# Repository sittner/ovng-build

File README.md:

OVNG-BUILD
==========
This repo contains the stuff to build a OpenVarioNG:

- KiCad project for the PCB
- FreeCAD drawing that includes the sensor distribution block and a printable housing
- buildroot env to build the sd card image for installation

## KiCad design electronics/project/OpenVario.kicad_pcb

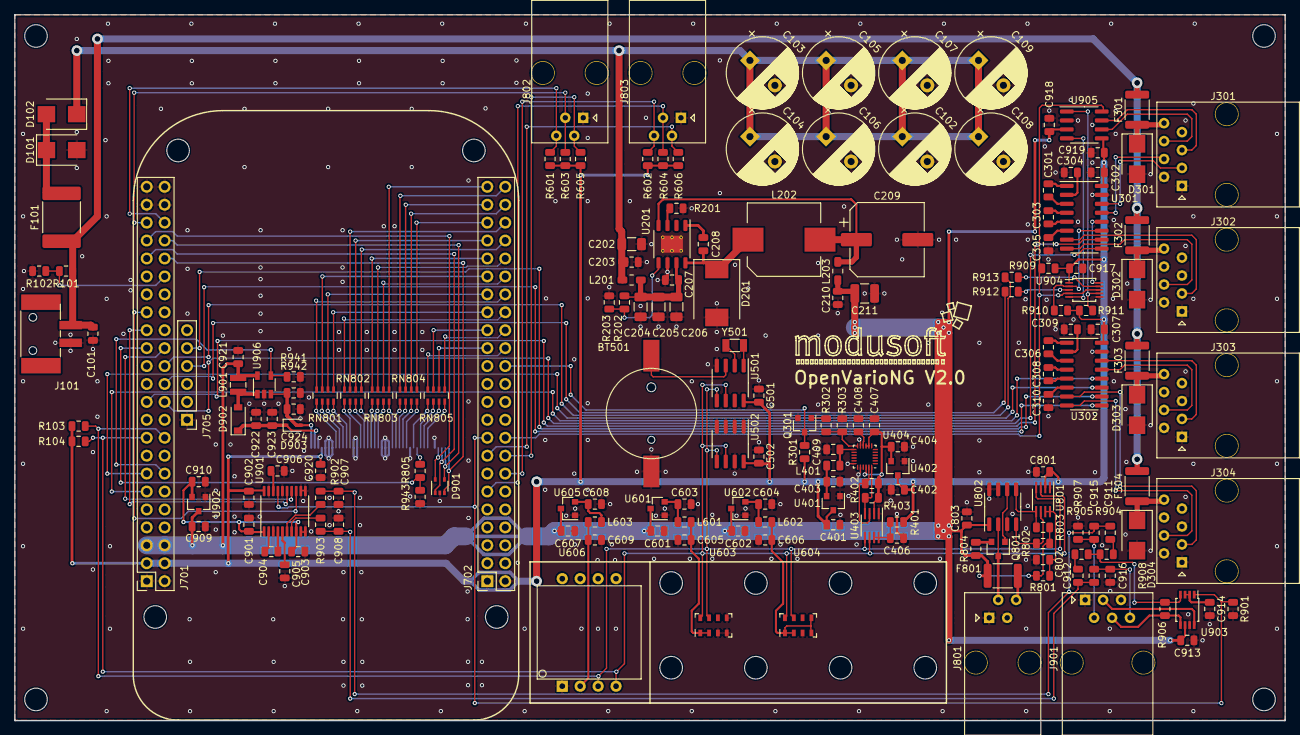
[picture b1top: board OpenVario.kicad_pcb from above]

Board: 2 copper layers, 180.0 x 100.0 mm, 200 parts (1 on the bottom side), 159 nets.

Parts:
BT501: CR-1220; BatteryHolder_HARWIN_S8411-45R_CR1220
C101, C203, C210, C302, C307, C406, C407, C408, C409, C501, C502, C605, C606, C609, C801, C802, C803, C901, C902, C903, C917, C918, C919, C920, C924: 100n; C_0805_2012Metric
C102, C103, C104, C105, C106, C107, C108, C109: 1000u/25V; CP_Radial_D10.0mm_P5.00mm
C202, C204, C205, C206: 4u7/50V; C_1206_3216Metric
C207: 1u/50V; C_0805_2012Metric
C208: 10n; C_0805_2012Metric
C209: 180u/16V; CP_Elec_10x7.9
C211: 47u/16V; C_1210_3225Metric
C301, C303, C304, C305, C306, C308, C309, C310, C401, C402, C403, C404, C601, C602, C603, C604, C607, C608, C909, C910, C913, C914, C915, C916, C922, C923: 1u; C_0805_2012Metric
C904, C905: 2u2; C_0805_2012Metric
C906, C921: 10u; C_0805_2012Metric
C907, C908: 2n2; C_0805_2012Metric
C911, C912: 470n; C_0805_2012Metric
D101: S3BB-13-F; D_SMB
D102: VS-20BQ030HM3/5BT; D_SMB
D201: SS36-E3/57T; D_SMC
D301, D302, D303, D304: S1BB-13-F; D_SMB
D901: PESD3V3L4UG; SOT-353_SC-70-5
D902: MBR0540; D_SOD-123
D903: MM3Z24VT1G; D_SOD-323
F101: 1.5A; Fuse_2920_7451Metric
F301, F302, F303, F304, F801: 300mA; Fuse_1812_4532Metric
H101, H102, H103, H104, H601, H602, H603, H604, H605, H606, H607, H608, H701, H702, H703, H704: M3; MountingHole_3.2mm_M3
J101: Power 12V; TerminalBlock_Phoenix_PTSM-0,5-2-HH-2.5-SMD_1x02-1MP_P2.50m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
J301: COM1; Modular-MEBP8-8S
J302: COM2; Modular-MEBP8-8S
J303: COM3; Modular-MEBP8-8S
J304: COM4; Modular-MEBP8-8S
J701: BeagleBone J9; PinSocket_2x23_P2.54mm_Vertical
J702: BeagleBone J8; PinSocket_2x23_P2.54mm_Vertical
J705: BeagleBone J1; PinHeader_1x06_P2.54mm_Vertical
J801: OneWire; Modular-MEBP4-4S
J802: ENC0; Modular-MEBP4-4S
J803: ENC1; Modular-MEBP4-4S
J901: Audio Out; Modular-MEBP6-6S
J902: DISP; TE_4-1734839-0_1x40-1MP_P0.5mm_Horizontal
L201, L203: 600R@100MHz/2A; WE_742792040
L202: 22u; L_Wuerth_WE-PDF_Handsoldering
L401, L601, L602, L603: 1k@100MHz; L_0805_2012Metric
L901: 10u; L_Wuerth_MAPI-2512
Q301: BC846; SOT-23
Q801: BSS84; SOT-23
R101: 120k; R_0805_2012Metric
R102, R301, R601, R602, R603, R604, R605, R606, R802, R803, R901, R909, R943: 10k; R_0805_2012Metric
R103, R104, R402, R403: 4k7; R_0805_2012Metric
R201: 61k9; R_0805_2012Metric
R202: 82k; R_0805_2012Metric
R203, R906: 20k; R_0805_2012Metric
R302, R303, R907, R908, R910, R911, R941: 100k; R_0805_2012Metric
R401, R801: 200k; R_0805_2012Metric
R804, R912, R913: 100R; R_0805_2012Metric
R805: 22R; R_0805_2012Metric
R902, R903: 470R; R_0805_2012Metric
R904, R905: 27k; R_0805_2012Metric
R942: 2R7; R_0805_2012Metric
RN801, RN802, RN803, RN804, RN805: 22R; R_Array_Concave_4x0603
U201: LM22670M-5_0; HSOP-8-1EP_3.9x4.9mm_P1.27mm_EP2.41x3.1mm_ThermalVias
U301, U302: MAX3232; SOIC-16_3.9x9.9mm_P1.27mm
U401, U402: MCP1700-1802E_SOT23; SOT-23
U403, U801: PCA9306; SSOP-8_2.95x2.8mm_P0.65mm
U404: ICM20948; QFN-24-1EP_3x3mm_P0.4mm_EP1.75x1.6mm_NP
U501: DS1338-33; SOIC-8_3.9x4.9mm_P1.27mm
U502: 24LC01; SOIC-8_3.9x4.9mm_P1.27mm
U601, U602, U605, U902: MCP1700-3302E_SOT23; SOT-23
U603, U604: MS5611; LGA-8_3x5mm_P1.25mm
U606: AMS5915
U802: DS2482-100; SOIC-8_3.9x4.9mm_P1.27mm
U901: PCM5101A; TSSOP-20_4.4x6.5mm_P0.65mm
U903: LM4990MM; TSSOP-8_3x3mm_P0.65mm
U904: TS3A24159DGSR; TSSOP-10_3x3mm_P0.5mm
U905: SN65HVDA540; SOIC-8_3.9x4.9mm_P1.27mm
U906: FAN5333B; TSOT-23-5
Y501: 32.768kHz/12.5pF; Crystal_SMD_3215-2Pin_3.2x1.5mm

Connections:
/5V Power Supply/Vin: C102.1, C103.1, C104.1, C105.1, C106.1, C107.1, C108.1, C109.1, C202.1, C203.1, D102.1, L201.1
/Audio Interface/+3V3: C302.2, C307.2, C401.1, C402.1, C501.2, C502.2, C801.2, C902.2, C917.2, C919.2, C920.2, J701.3, J701.4, J902.4, R103.1, R104.1, R301.2, R401.1, R601.1, R602.1, R603.1, R604.1, R605.1, R606.1, R909.1, R910.1, R911.1, U301.16, U302.16, U401.3, U402.3, U501.8, U502.8, U801.2, U901.20, U904.1, U905.5
/Audio Interface/+5V: C210.1, C211.1, C601.1, C602.1, C607.1, C803.2, C909.1, C913.1, C918.2, C921.2, F801.1, J701.5, J701.6, L203.2, L901.2, R801.2, R802.1, R803.1, R804.1, U601.3, U602.3, U605.3, U802.1, U902.3, U903.6, U905.3, U906.5
/Audio Interface/AUD_L: C907.1, C911.1, C915.1, R902.1
/Audio Interface/AUD_R: C908.1, C912.1, C916.1, R903.1
/Audio Interface/AVDD: C901.2, C903.2, C910.1, U901.1, U901.8, U902.2
/Audio Interface/BCK: J701.31, U901.13
/Audio Interface/DIN: J701.28, U901.14
/Audio Interface/ENA: J702.17, R901.2, U901.17, U903.1
/BeagleBone+Display/AIN5: J701.36, R101.2, R102.1
/BeagleBone+Display/BL_LED_A: C922.2, C923.2, D902.1, D903.1, J902.2
/BeagleBone+Display/BL_LED_K: C924.2, D903.2, J902.1, R942.2, U906.3
/BeagleBone+Display/GPIO0_7: J701.42, J802.4, R601.2
/BeagleBone+Display/GPIO0_20: J701.41, J802.3, R603.2
/BeagleBone+Display/GPIO0_26: J702.14, J803.4, R602.2
/BeagleBone+Display/GPIO1_13: J702.11, J803.3, R604.2
/BeagleBone+Display/GPIO1_14: J702.16, J802.2, R605.2
/BeagleBone+Display/GPIO1_15: J702.15, J803.2, R606.2
/BeagleBone+Display/GPIO2_1: J702.18, R909.2, U904.4, U904.8, U905.8
/BeagleBone+Display/I2C1_SCL: J701.17, R104.2, U403.6, U501.6, U502.6, U603.8, U604.8, U606.4, U801.3
/BeagleBone+Display/I2C1_SDA: J701.18, R103.2, U403.5, U501.5, U502.5, U603.7, U604.7, U606.3, U801.4
/BeagleBone+Display/I2S_LRCK: J701.29, U901.15
/BeagleBone+Display/IMU_IRQ: J702.26, Q301.3, R301.1
/BeagleBone+Display/LCD_BL_PWM: J701.14, R941.2, U906.4
/BeagleBone+Display/LCD_D0: J702.45, RN803.5
/BeagleBone+Display/LCD_D1: J702.46, RN804.8
/BeagleBone+Display/LCD_D2: J702.43, RN804.7
/BeagleBone+Display/LCD_D3: J702.44, RN804.6
/BeagleBone+Display/LCD_D4: J702.41, RN804.5
/BeagleBone+Display/LCD_D5: J702.42, RN802.7
/BeagleBone+Display/LCD_D6: J702.39, RN802.6
/BeagleBone+Display/LCD_D7: J702.40, RN802.5
/BeagleBone+Display/LCD_D8: J702.37, RN803.8
/BeagleBone+Display/LCD_D9: J702.38, RN803.7
/BeagleBone+Display/LCD_D10: J702.36, RN803.6
/BeagleBone+Display/LCD_D11: J702.34, RN801.8
/BeagleBone+Display/LCD_D12: J702.35, RN801.7
/BeagleBone+Display/LCD_D13: J702.33, RN801.6
/BeagleBone+Display/LCD_D14: J702.31, RN801.5
/BeagleBone+Display/LCD_D15: J702.32, RN802.8
/BeagleBone+Display/LCD_DISPEN: J701.27, R805.1, R943.2
/BeagleBone+Display/LCD_EN: J702.30, RN805.5
/BeagleBone+Display/LCD_HSYNC: J702.29, RN805.7
/BeagleBone+Display/LCD_PCLK: J702.28, RN805.8
/BeagleBone+Display/LCD_VSYNC: J702.27, RN805.6
/BeagleBone+Display/TOUCH_XL: D901.4, J701.40, J902.39
/BeagleBone+Display/TOUCH_XR: D901.5, J701.39, J902.37
/BeagleBone+Display/TOUCH_YD: D901.1, J701.37, J902.38
/BeagleBone+Display/TOUCH_YU: D901.3, J701.38, J902.40
/BeagleBone+Display/UART0_RXD: J705.4, U302.9
/BeagleBone+Display/UART0_TXD: J705.5, U302.10
/RS232 Interfaces/+12V: C101.1, F101.2, F301.2, F302.2, F303.2, F304.2, J101.2, R101.1
/RS232 Interfaces/CAN0_H: J301.5, U905.7
/RS232 Interfaces/CAN0_L: J301.6, U905.6
/RS232 Interfaces/CAN0_RXD_I: U904.5, U905.4
/RS232 Interfaces/CAN0_TXD_I: R911.2, U904.7, U905.1
/RS232 Interfaces/UART0_RXD: J701.26, R913.1
/RS232 Interfaces/UART0_RXD_I: U301.12, U904.10
/RS232 Interfaces/UART0_TXD: J701.24, R912.1
/RS232 Interfaces/UART0_TXD_I: R910.2, U301.11, U904.2
/RS232 Interfaces/UART1_RXD: J701.22, U301.9
/RS232 Interfaces/UART1_TXD: J701.21, U301.10
/RS232 Interfaces/UART2_RXD: J701.11, U302.12
/RS232 Interfaces/UART2_TXD: J701.13, U302.11
GND: BT501.2, C101.2, C102.2, C103.2, C104.2, C105.2, C106.2, C107.2, C108.2, C109.2, C202.2, C203.2, C204.2, C205.2, C206.2, C207.2, C209.2, C210.2, C211.2, C302.1, C304.1, C305.1, C307.1, C309.1, C310.1, C401.2, C402.2, C403.2, C404.2, C406.1, C407.1, C408.2, C409.1, C501.1, C502.1, C601.2, C602.2, C603.2, C604.2, C605.2, C606.2, C607.2, C608.2, C609.2, C801.1, C802.1, C803.1, C901.1, C902.1, C903.1, C905.2, C906.2, C907.2, C908.2, C909.2, C910.2, C913.2, C914.1, C917.1, C918.1, C919.1, C920.1, C921.1, C922.1, C923.1, C924.1, D101.2, D201.2, D301.2, D302.2, D303.2, D304.2, D901.2, J101.1, J301.1, J301.2, J302.1, J302.2, J302.5, J303.1, J303.2, J303.5, J304.1, J304.2, J304.5, J701.1, J701.2, J701.43, J701.44, J701.45, J701.46, J702.1, J702.2, J705.1, J801.1, J801.3, J802.1, J803.1, J901.1, J901.5, J902.3, J902.5, J902.6, J902.7, J902.13, J902.14, J902.21, J902.22, J902.23, J902.29, J902.36, Q301.2, R102.2, R201.2, R203.2, R303.1, R901.1, R907.1, R908.1, R941.1, R942.1, R943.1, U201.6, U201.9, U301.15, U302.15, U401.1, U402.1, U403.1, U404.11, U404.18, U404.20, U501.4, U502.1, U502.2, U502.3, U502.4, U502.7, U601.1, U602.1, U603.3, U603.4, U603.5, U604.3, U605.1, U606.1, U801.1, U802.3, U802.7, U802.8, U901.3, U901.9, U901.10, U901.11, U901.12, U901.16, U901.19, U902.1, U903.7, U904.6, U905.2, U906.2
unnamed: BT501.1, U501.3
unnamed: C204.1, C205.1, C206.1, C207.1, L201.2, R202.1, U201.7
unnamed: C208.1, D201.1, L202.1, U201.8
unnamed: C208.2, U201.1
unnamed: C209.1, L202.2, L203.1, U201.4
unnamed: C301.1, U301.1
unnamed: C301.2, U301.3
unnamed: C303.1, U301.4
unnamed: C303.2, U301.5
unnamed: C304.2, U301.2
unnamed: C305.2, U301.6
unnamed: C306.1, U302.1
unnamed: C306.2, U302.3
unnamed: C308.1, U302.4
unnamed: C308.2, U302.5
unnamed: C309.2, U302.2
unnamed: C310.2, U302.6
unnamed: C403.1, L401.1, U401.2
unnamed: C404.1, C407.2, R402.1, R403.1, U402.2, U403.2, U404.8, U404.9, U404.22
unnamed: C406.2, R401.2, U403.7, U403.8
unnamed: C408.1, U404.10
unnamed: C409.2, L401.2, U404.13
unnamed: C603.1, L601.1, U601.2
unnamed: C604.1, L602.1, U602.2
unnamed: C605.1, L601.2, U603.1, U603.2
unnamed: C606.1, L602.2, U604.1, U604.2, U604.4, U604.5
unnamed: C608.1, L603.1, U605.2
unnamed: C609.1, L603.2, U606.2
unnamed: C802.2, R801.1, U801.7, U801.8
unnamed: C904.1, U901.2
unnamed: C904.2, U901.4
unnamed: C905.1, U901.5
unnamed: C906.1, U901.18
unnamed: C911.2, R904.2
unnamed: C912.2, R905.2
unnamed: C914.2, U903.2, U903.3
unnamed: C915.2, J901.2, R907.2
unnamed: C916.2, J901.6, R908.2
unnamed: D101.1, D102.2, F101.1
unnamed: D301.1, F301.1, J301.8
unnamed: D302.1, F302.1, J302.8
unnamed: D303.1, F303.1, J303.8
unnamed: D304.1, F304.1, J304.8
unnamed: D902.2, L901.1, U906.1
unnamed: F801.2, J801.4
unnamed: J301.3, U301.14
unnamed: J301.4, U301.13
unnamed: J302.3, U301.7
unnamed: J302.4, U301.8
unnamed: J303.3, U302.14
unnamed: J303.4, U302.13
unnamed: J304.3, U302.7
unnamed: J304.4, U302.8
unnamed: J801.2, Q801.3, U802.2
unnamed: J901.3, U903.8
unnamed: J901.4, R906.1, U903.5
unnamed: J902.8, RN801.1
unnamed: J902.9, RN801.2
unnamed: J902.10, RN801.3
unnamed: J902.11, RN801.4
unnamed: J902.12, RN802.1
unnamed: J902.15, RN802.2
unnamed: J902.16, RN802.3
unnamed: J902.17, RN802.4
unnamed: J902.18, RN803.1
unnamed: J902.19, RN803.2
unnamed: J902.20, RN803.3
unnamed: J902.24, RN803.4
unnamed: J902.25, RN804.1
unnamed: J902.26, RN804.2
unnamed: J902.27, RN804.3
unnamed: J902.28, RN804.4
unnamed: J902.30, RN805.1
unnamed: J902.31, R805.2
unnamed: J902.32, RN805.2
unnamed: J902.33, RN805.3
unnamed: J902.34, RN805.4
unnamed: Q301.1, R302.2
unnamed: Q801.1, U802.6
unnamed: Q801.2, R804.2
unnamed: R201.1, U201.3
unnamed: R202.2, R203.1, U201.5
unnamed: R302.1, R303.2, U404.12
unnamed: R402.2, U403.3, U404.23
unnamed: R403.2, U403.4, U404.24
unnamed: R802.2, U801.6, U802.4
unnamed: R803.2, U801.5, U802.5
unnamed: R902.2, U901.6
unnamed: R903.2, U901.7
unnamed: R904.1, R905.1, R906.2, U903.4
unnamed: R912.2, U904.3
unnamed: R913.2, U904.9
unnamed: U501.1, Y501.2
unnamed: U501.2, Y501.1

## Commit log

2020-12-01 added kicad files
2020-12-01 moved project files to project folder
2020-12-01 added 3d models of custom parts
2020-12-01 added mechanical drawing
2020-12-01 added partlist
2020-12-01 added buildroot 2020.02.8 as submodule
2020-12-01 added .gitignore file
2020-12-01 moved back to buildroot 2019.02.11 for git migration
2020-12-01 added license and README
2020-12-01 added stl files for printing the housing
2020-12-01 added stl files sensor-block and display spacer STLs
2020-12-02 checked out buildroot 2020.02.8
2020-12-02 fixed legacy config options
2020-12-02 updated kernel to 4.19.94-ti-r57
2020-12-02 moved to buildroot-2020.02.8, cleanup dtoverlays and u-boot config
2020-12-03 renamed ovng-overlays, detect device tree file, be verbose on loading files on bootloader
2020-12-03 fixed housing for use with BeagleBone green (not wireless)
2020-12-03 updated stl files
2020-12-04 fixed label alignment
2020-12-04 added schematic and placement as pdf
2020-12-05 user ovng reporo for xcsoar patching, update to 6.8.17
2020-12-05 added production files for sensor-block
2020-12-09 first working sgx/weston config
2020-12-09 added weston startup/config stuff
2020-12-10 moved to upstream xcsoar and add wayland patches
2020-12-10 removed unused packages
2020-12-10 added xcsoar ovng support patch
2020-12-10 fixed weston.ini
2020-12-10 cleanup weston settings
2020-12-11 xcsoar wayland fullscreen detects size automatically
2020-12-11 use syslog ringbuffer
2020-12-11 fixed xcsoar dependencies
2020-12-11 fixed type in init script
2020-12-13 fix xcsoar startup config for weston
2020-12-13 changed config for ro root fs
2020-12-13 added initial version of emmc install script
2020-12-13 wasit for weston to be ready on startup
2020-12-13 start touch calib on first start, fix weston config for ro root fs
2020-12-14 fixed some config issues
2020-12-14 added tech drawing for display spacer
2020-12-14 backport KRT2 device support
2020-12-15 disable weston panel
2020-12-15 added GTK3 for config menu
2020-12-16 added NLS support (en+de)
2020-12-16 set seeed LCD as default display
2020-12-16 fixed config eeprom type
2020-12-21 fixed emmc cleanup in install-emmc.sh
2020-12-21 create dest directory in weston-calibrator-helper
2021-04-24 updated icm20948 driver
2021-04-24 updated ovng-overlays
2021-04-24 use seperate NMEA message type for AHRS data
2021-04-24 updated ovngd, use config file
2022-04-04 updated pcb file
2022-04-04 set LANG variable in wayland_env
2022-04-04 added wayland sound support to xcsoar
2022-04-04 set screen orientation to 0
2022-04-04 updated gitignore file
2022-04-04 completed install-emmc script
2022-04-04 added display spacer cut for emi shielding conductor
2022-04-04 added printable version of SensorBlock
2022-04-04 set uboot CONFIG_ENV_FAT_DEVICE_AND_PART to allow updating of boot partition on SW updates
